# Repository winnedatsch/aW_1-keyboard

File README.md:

# aW_1 Keyboard

This repository contains the PCB, case design, and firmware for the aW_1 split (semi-)wireless keyboard. The aW_1 layout is a modification of the ErgoDox layout with straightened rows and removed thumb clusters. It is therefore fully compatible with ErgoDox keysets. It is compatible with the [ZMK](https://zmk.dev/) keyboard firmware.

## Design Philosophy
The aW_1 is based on the Nordic NRF52832 that provides both the CPU and bluetooth module in a single chip, which allows for lower power consumption. It can be operated from a standard JST-connected battery, or plugged in via USB-C, which will simultaneously charge the battery. The two keyboard halves are connected with a USB-C cable, hence the "semi"-wireless, with the right half containing most of the circuitry and the left only containing an IO expander. A different approach would be the one pursued by the Mitosis (https://www.reddit.com/r/MechanicalKeyboards/comments/66588f/wireless_split_qmk_mitosis/), which does require a dongle that both halves communicate to. I prioritized the ability to quickly connect the keyboard to laptops, mobile devices, etc. and potential pairing of multiple devices at the same time over cutting the last remaining wire. The connection between the halves is USB-C instead of TRRS because TRRS is not hot-pluggable. Like with an ErgoDox, the there is only a single reversible PCB design for both halves, which makes it cheaper to order. 

## Folder Structure
- `case`: Contains the DXF Files for a low-cost case design built from 5 layers of laser-cut acrylic. 
- `firmware/custom`: Contains a custom firmware implemented with the [Zephyr RTOS](https://www.zephyrproject.org/). The firmware implements all the essential functionality expected of a keyboard firmware (Bluetooth connectivity, layout customization, sleep mode), but lacks some important features (advanced layer config, multiple Bluetooth profiles, etc.). It has mainly served as an educational effort, but for day-to-day usage the ZMK firmware is recommended (see below).
- `firmware/zmk`: Contains the board configuration for the [ZMK](https://zmk.dev/) keyboard firmware. This firmware is recommended for regular use, as it is more stable, customizable, and offers additional features.
- `pcb`: Contains the KiCAD schematics and layout files for the reversible PCB.

## ZMK Setup & Flashing
Due to the [very strict licensing requirements of ZMK](https://zmk.dev/docs/development/clean-room), the board configuration for the GPL-licensed aW_1 cannot be added to ZMK's main repository. Fortunately, flashing the firmware is still a relatively simple process:

1. Setup ZMK locally by following its [Toolchain Setup](https://zmk.dev/docs/development/setup) guide. Let `{zmk}` be the local folder that you have cloned the ZMK main repository into. 
2. Copy the `firmware/zmk/aW_1` folder from this repository into `{zmk}/app/boards`.
3. Switch to the `{zmk}/app` folder and run `west build -b aW_1`.
4. Install the [Nordic nRF Command Line Tools](https://www.nordicsemi.com/Products/Development-tools/nrf-command-line-tools) (including the separate install of the [Segger drivers for J-Link](https://www.segger.com/downloads/jlink/#J-LinkSoftwareAndDocumentationPack) on MacOS and Linux). 
5. Connect the keyboard to your computer with your choice of [Segger J-Link](https://www.segger.com/products/debug-probes/j-link/).
6. Run `west flash` in the `{zmk}/app` directory.

That's it! Your keyboard should now show up as a Bluetooth device. If not, try restarting the keyboard by switching the power switch off and on again.

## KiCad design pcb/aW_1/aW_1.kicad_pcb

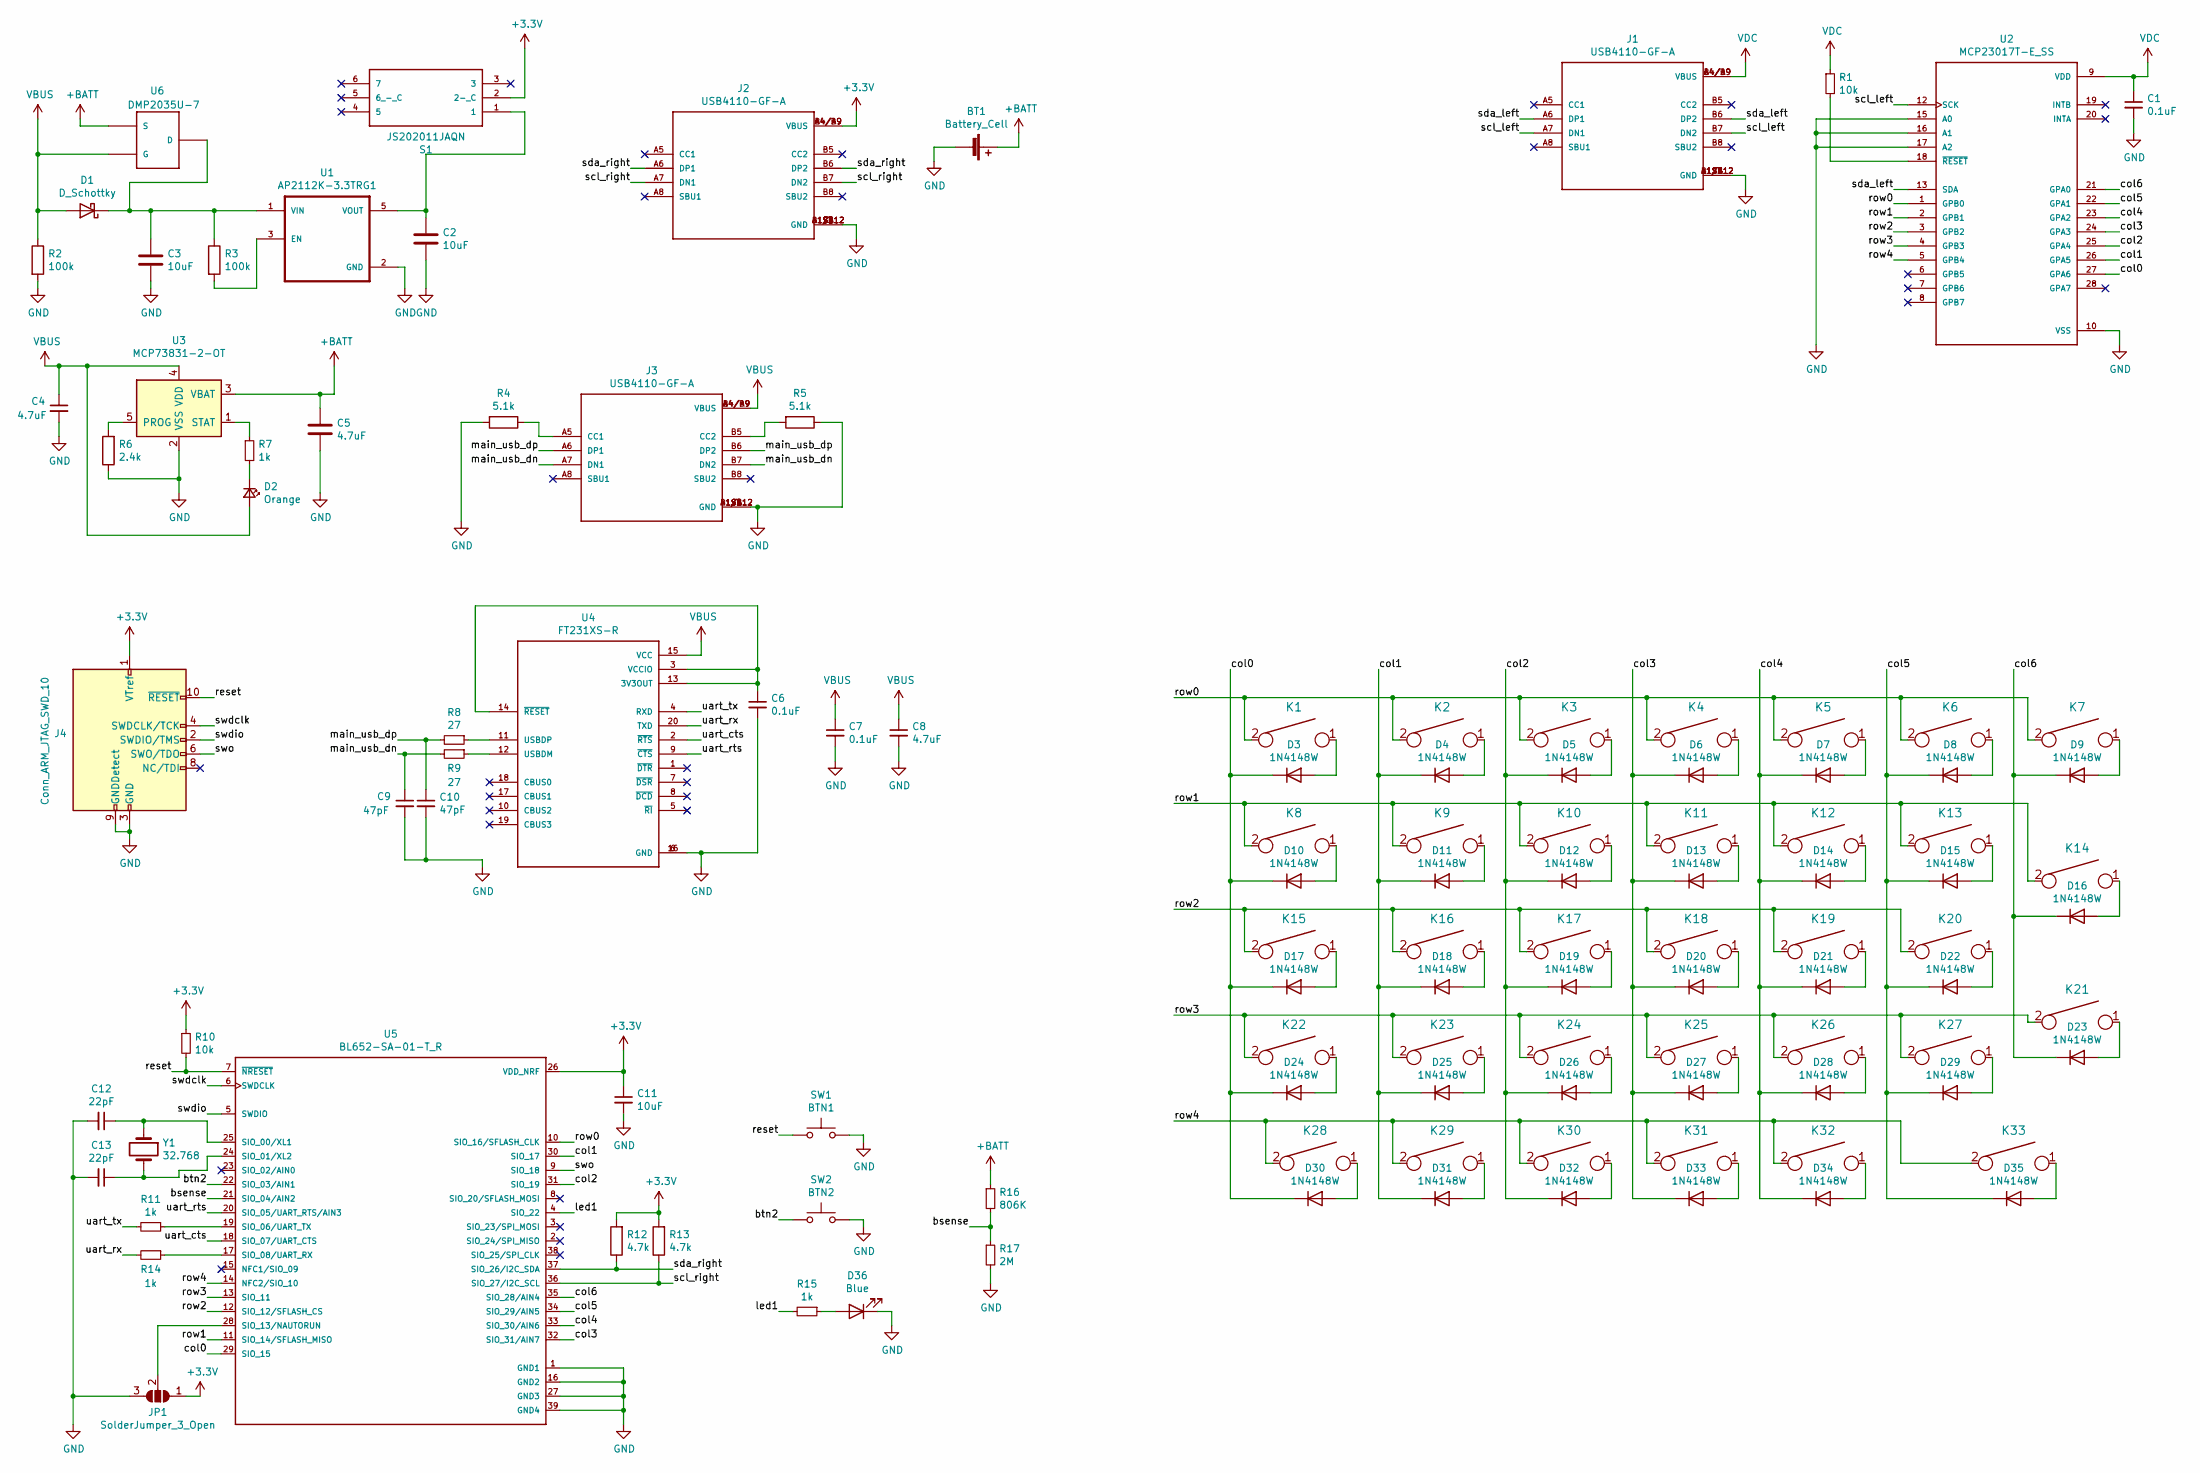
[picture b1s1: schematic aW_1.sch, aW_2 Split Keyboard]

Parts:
BT1: Battery_Cell; JST_S2B-PH-SM4-TB(LF)(SN)
C1, C6, C7: 0.1uF; C_0402_1005Metric
C2, C3, C11: 10uF; C_0603_1608Metric
C4, C5, C8: 4.7uF; C_0402_1005Metric
C9, C10: 47pF; C_0402_1005Metric
C12, C13: 22pF; C_0402_1005Metric
D1: D_Schottky; D_SOD-123
D2: Orange; LED_0805_2012Metric
D3, D4, D5, D6, D7, D8, D9, D10, D11, D12, D13, D14, D15, D16, D17, D18, D19, D20, D21, D22, D23, D24, D25, D26, D27, D28, D29, D30, D31, D32, D33, D34, D35: 1N4148W; D_SOD-123_mirrored
D36: Blue; LED_0805_2012Metric
J1, J2, J3: USB4110-GF-A; GCT_USB4110-GF-A
J4: Conn_ARM_JTAG_SWD_10; PinHeader_2x05_P1.27mm_Vertical
JP1: SolderJumper_3_Open; SolderJumper-3_P1.3mm_Open_RoundedPad1.0x1.5mm
K1, K8, K14, K15, K21, K22: KEYSW; Mx_Alps_150
K2, K3, K4, K5, K6, K7, K9, K10, K11, K12, K13, K16, K17, K18, K19, K20, K23, K24, K25, K26, K27, K28, K29, K30, K31, K32: KEYSW; Mx_Alps_100
K33: KEYSW; Mx_Alps_200
R1, R10: 10k; R_0402_1005Metric
R2, R3: 100k; R_0402_1005Metric
R4, R5: 5.1k; R_0402_1005Metric
R6: 2.4k; R_0402_1005Metric
R7, R11, R14, R15: 1k; R_0402_1005Metric
R8, R9: 27; R_0402_1005Metric
R12, R13: 4.7k; R_0402_1005Metric
R16: 806K; R_0603_1608Metric
R17: 2M; R_0603_1608Metric
S1: JS202011JAQN
SW1: BTN1; SW_KMR221GLFS
SW2: BTN2; SW_KMR221GLFS
U1: AP2112K-3.3TRG1; SOT95P285X140-5N
U2: MCP23017T-E_SS; SOP65P780X200-28N
U3: MCP73831-2-OT; SOT-23-5
U4: FT231XS-R; SOP63P599X175-20N
U5: BL652-SA-01-T_R; XCVR_BL652-SA-01-T
U6: DMP2035U-7; SOT23
Y1: 32.768; XTAL_ECS-.327-12.5-34B-TR

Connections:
+3V3: C11.1, J2.A4/B9 (VBUS), J2.B4/A9 (VBUS), J4.1 (VTref), JP1.1 (A), R10.1, R12.2, R13.2, S1.2 (2-_C), U5.26 (VDD_NRF)
+BATT: BT1.1 (+), C5.1, R16.1, U3.3 (VBAT), U6.2 (S)
/bsense: R16.2, R17.1, U5.21 (SIO_04/AIN2)
/btn2: SW2.1, U5.22 (SIO_03/AIN1)
/col0: D3.1 (K), D10.1 (K), D17.1 (K), D24.1 (K), D30.1 (K), U2.27 (GPA6), U5.29 (SIO_15)
/col1: D4.1 (K), D11.1 (K), D18.1 (K), D25.1 (K), D31.1 (K), U2.26 (GPA5), U5.30 (SIO_17)
/col2: D5.1 (K), D12.1 (K), D19.1 (K), D26.1 (K), D32.1 (K), U2.25 (GPA4), U5.31 (SIO_19)
/col3: D6.1 (K), D13.1 (K), D20.1 (K), D27.1 (K), D33.1 (K), U2.24 (GPA3), U5.32 (SIO_31/AIN7)
/col4: D7.1 (K), D14.1 (K), D21.1 (K), D28.1 (K), D34.1 (K), U2.23 (GPA2), U5.33 (SIO_30/AIN6)
/col5: D8.1 (K), D15.1 (K), D22.1 (K), D29.1 (K), D35.1 (K), U2.22 (GPA1), U5.34 (SIO_29/AIN5)
/col6: D9.1 (K), D16.1 (K), D23.1 (K), U2.21 (GPA0), U5.35 (SIO_28/AIN4)
/led1: R15.2, U5.4 (SIO_22)
/main_usb_dn: C9.1, J3.A7 (DN1), J3.B7 (DN2), R9.2
/main_usb_dp: C10.1, J3.A6 (DP1), J3.B6 (DP2), R8.2
/reset: J4.10 (~RESET~), R10.2, SW1.1, U5.7 (~NRESET~)
/row0: K1.2, K2.2, K3.2, K4.2, K5.2, K6.2, K7.2, U2.1 (GPB0), U5.10 (SIO_16/SFLASH_CLK)
/row1: K8.2, K9.2, K10.2, K11.2, K12.2, K13.2, K14.2, U2.2 (GPB1), U5.11 (SIO_14/SFLASH_MISO)
/row2: K15.2, K16.2, K17.2, K18.2, K19.2, K20.2, U2.3 (GPB2), U5.12 (SIO_12/SFLASH_CS)
/row3: K21.2, K22.2, K23.2, K24.2, K25.2, K26.2, K27.2, U2.4 (GPB3), U5.13 (SIO_11)
/row4: K28.2, K29.2, K30.2, K31.2, K32.2, K33.2, U2.5 (GPB4), U5.14 (NFC2/SIO_10)
/scl_left: J1.A7 (DN1), J1.B7 (DN2), U2.12 (SCK)
/scl_right: J2.A7 (DN1), J2.B7 (DN2), R13.1, U5.36 (SIO_27/I2C_SCL)
/sda_left: J1.A6 (DP1), J1.B6 (DP2), U2.13 (SDA)
/sda_right: J2.A6 (DP1), J2.B6 (DP2), R12.1, U5.37 (SIO_26/I2C_SDA)
/swdclk: J4.4 (SWDCLK/TCK), U5.6 (SWDCLK)
/swdio: J4.2 (SWDIO/TMS), U5.5 (SWDIO)
/swo: J4.6 (SWO/TDO), U5.9 (SIO_18)
/uart_cts: U4.2 (~RTS~), U5.18 (SIO_07/UART_CTS)
/uart_rts: U4.9 (~CTS~), U5.20 (SIO_05/UART_RTS/AIN3)
/uart_rx: R14.2, U4.20 (TXD)
/uart_tx: R11.2, U4.4 (RXD)
GND: BT1.2 (-), C1.2, C2.2, C3.2, C4.2, C5.2, C6.2, C7.2, C8.2, C9.2, C10.2, C11.2, C12.2, C13.2, D36.1 (K), J1.A1/B12 (GND), J1.B1/A12 (GND), J1.S1 (GND), J1.S2 (GND), J1.S3 (GND), J1.S4 (GND), J2.A1/B12 (GND), J2.B1/A12 (GND), J2.S1 (GND), J2.S2 (GND), J2.S3 (GND), J2.S4 (GND), J3.A1/B12 (GND), J3.B1/A12 (GND), J3.S1 (GND), J3.S2 (GND), J3.S3 (GND), J3.S4 (GND), J4.3 (GND), J4.5 (GND), J4.9 (GNDDetect), JP1.3 (B), R2.2, R4.2, R5.1, R6.1, R17.2, SW1.2, SW2.2, U1.2 (GND), U2.10 (VSS), U2.15 (A0), U2.16 (A1), U2.17 (A2), U3.2 (VSS), U4.6 (GND), U4.16 (GND), U5.1 (GND1), U5.16 (GND2), U5.27 (GND3), U5.39 (GND4)
unnamed: C2.1, S1.1, U1.5 (VOUT)
unnamed: C3.1, D1.1 (K), R3.1, U1.1 (VIN), U6.3 (D)
unnamed: C6.1, U4.3 (VCCIO), U4.13 (3V3OUT), U4.14 (~RESET~)
unnamed: C12.1, U5.25 (SIO_00/XL1), Y1.1
unnamed: C13.1, U5.24 (SIO_01/XL2), Y1.2
unnamed: D2.1 (K), R7.2
unnamed: D3.2 (A), K1.1
unnamed: D4.2 (A), K2.1
unnamed: D5.2 (A), K3.1
unnamed: D6.2 (A), K4.1
unnamed: D7.2 (A), K5.1
unnamed: D8.2 (A), K6.1
unnamed: D9.2 (A), K7.1
unnamed: D10.2 (A), K8.1
unnamed: D11.2 (A), K9.1
unnamed: D12.2 (A), K10.1
unnamed: D13.2 (A), K11.1
unnamed: D14.2 (A), K12.1
unnamed: D15.2 (A), K13.1
unnamed: D16.2 (A), K14.1
unnamed: D17.2 (A), K15.1
unnamed: D18.2 (A), K16.1
unnamed: D19.2 (A), K17.1
unnamed: D20.2 (A), K18.1
unnamed: D21.2 (A), K19.1
unnamed: D22.2 (A), K20.1
unnamed: D23.2 (A), K21.1
unnamed: D24.2 (A), K22.1
unnamed: D25.2 (A), K23.1
unnamed: D26.2 (A), K24.1
unnamed: D27.2 (A), K25.1
unnamed: D28.2 (A), K26.1
unnamed: D29.2 (A), K27.1
unnamed: D30.2 (A), K28.1
unnamed: D31.2 (A), K29.1
unnamed: D32.2 (A), K30.1
unnamed: D33.2 (A), K31.1
unnamed: D34.2 (A), K32.1
unnamed: D35.2 (A), K33.1
unnamed: D36.2 (A), R15.1
unnamed: J3.A5 (CC1), R4.1
unnamed: J3.B5 (CC2), R5.2
unnamed: JP1.2 (C), U5.28 (SIO_13/NAUTORUN)
unnamed: R1.2, U2.18 (~RESET~)
unnamed: R3.2, U1.3 (EN)
unnamed: R6.2, U3.5 (PROG)
unnamed: R7.1, U3.1 (STAT)
unnamed: R8.1, U4.11 (USBDP)
unnamed: R9.1, U4.12 (USBDM)
unnamed: R11.1, U5.19 (SIO_06/UART_TX)
unnamed: R14.1, U5.17 (SIO_08/UART_RX)
VBUS: C4.1, C7.1, C8.1, D1.2 (A), D2.2 (A), J3.A4/B9 (VBUS), J3.B4/A9 (VBUS), R2.1, U3.4 (VDD), U4.15 (VCC), U6.1 (G)
VDC: C1.1, J1.A4/B9 (VBUS), J1.B4/A9 (VBUS), R1.1, U2.9 (VDD)

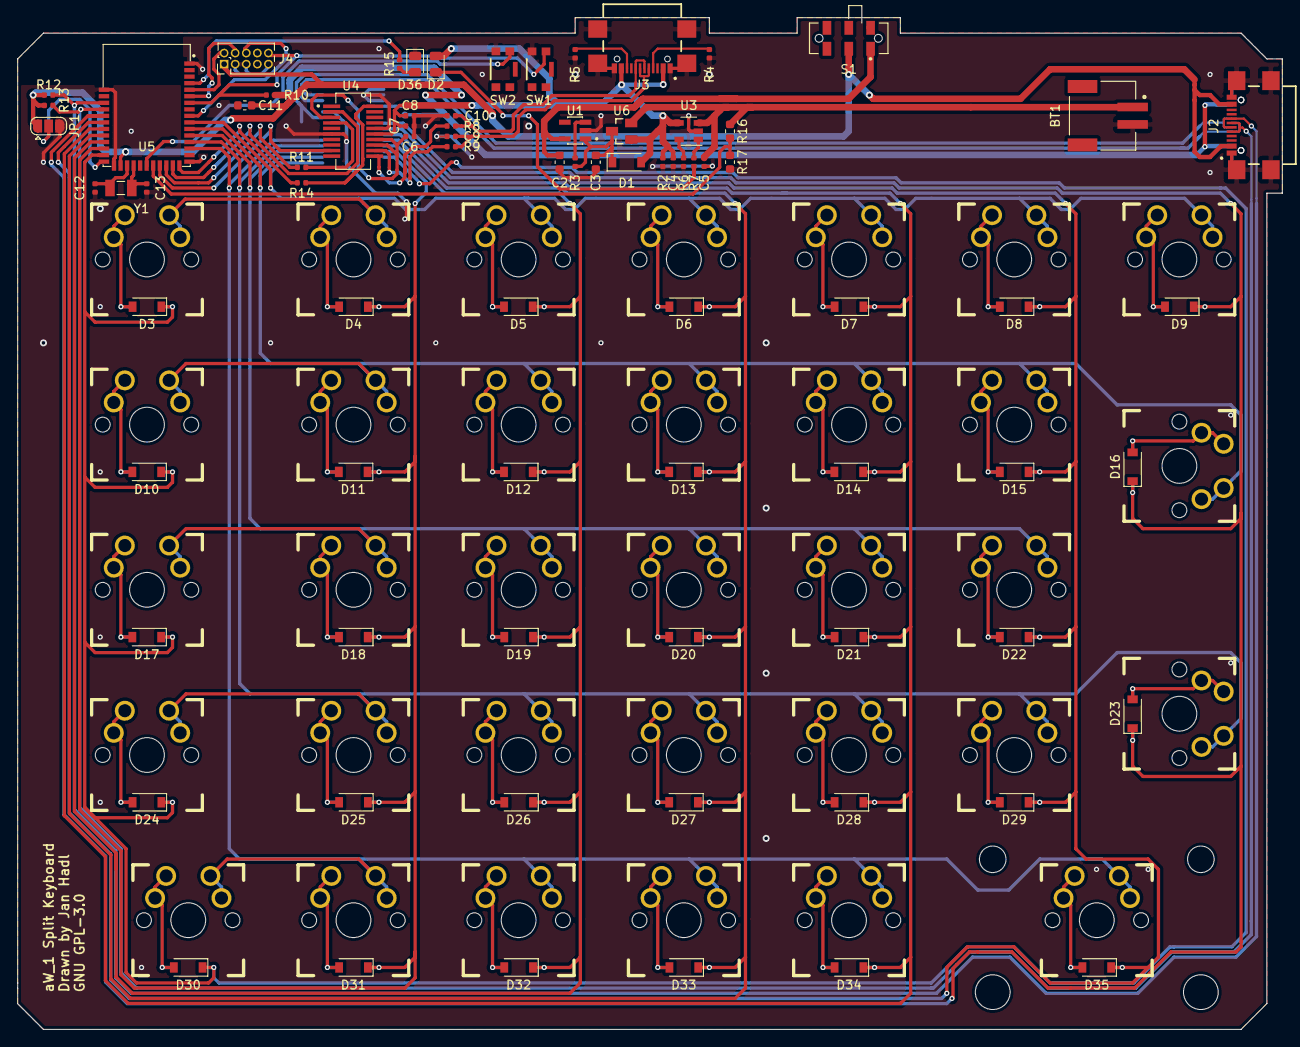
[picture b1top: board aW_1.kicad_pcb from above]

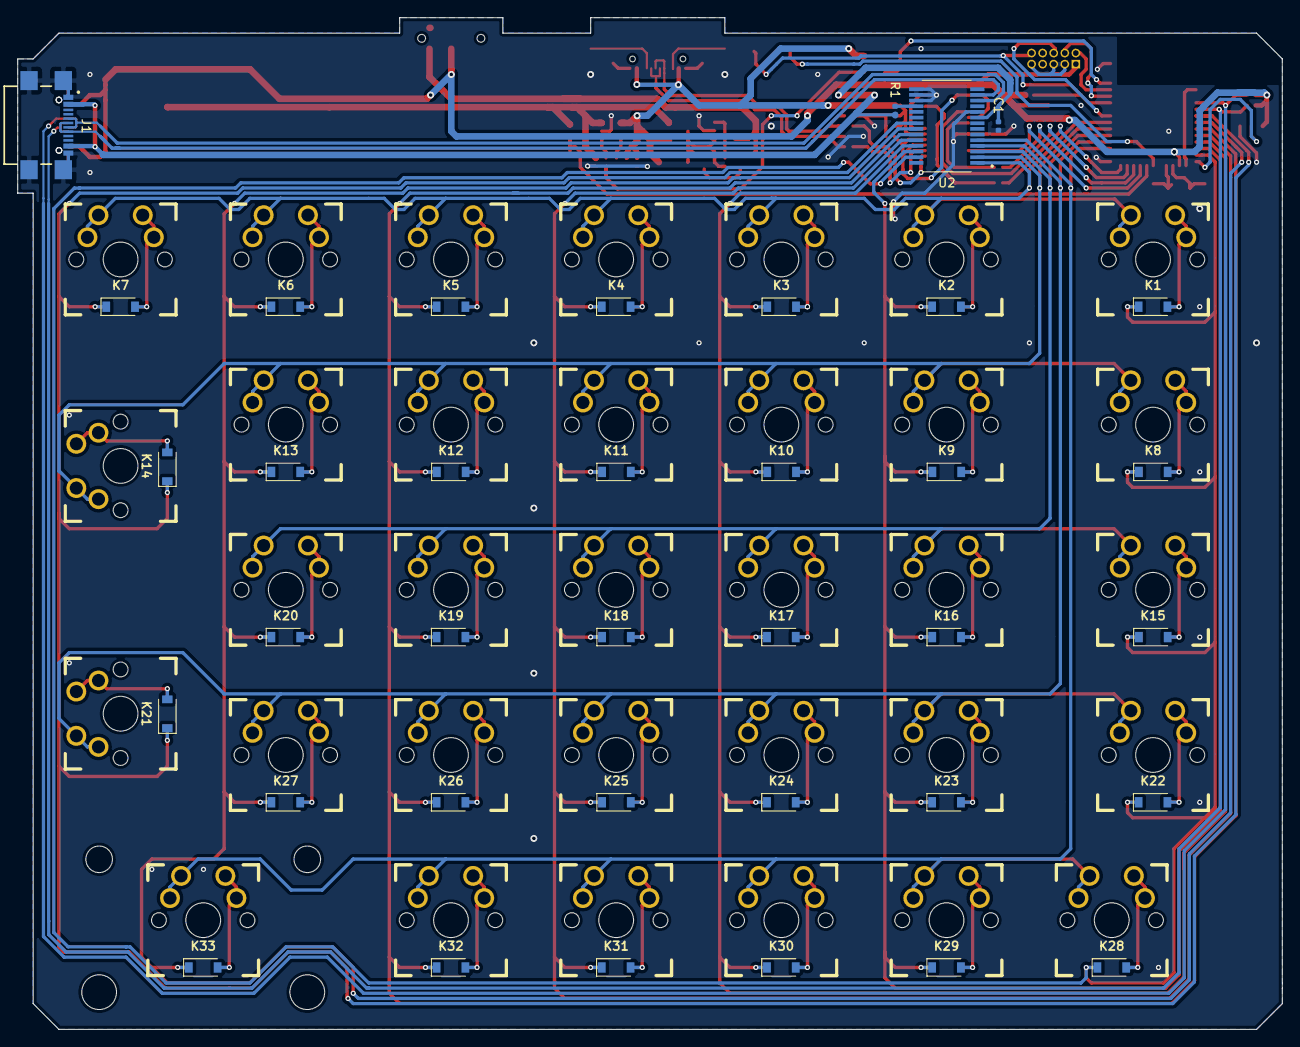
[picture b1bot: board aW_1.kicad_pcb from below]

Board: 2 copper layers, 145.1 x 116.1 mm, 115 parts (4 on the bottom side), 85 nets.

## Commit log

2020-04-10 Zephyr and PlatformIO board config; blinky example
2020-04-11 Converted code to CPP, added matrix scanning code
2020-04-19 Incomplete implementation of BLE HID service
2020-04-22 modified BLE hid implementation, but not working yet
2020-04-26 Fixed HID config, input works now; connection on mobile still fails
2020-05-11 added battery reporting
2020-05-15 Added support for left keyboard half over i2c
2020-05-24 first draft of board schematic
2020-05-31 Added USB controller and reset button
2020-06-01 Added additional leds and buttons, decoupling capacitors, component mappings
2020-06-14 Finished keyboard matrix wiring, left side wiring
2020-06-19 (Almost) finished pcb, few GND connections missing
2020-06-21 Traces and pours finished
2020-06-24 Fixed silk screen and fab layers
2020-06-26 Added gerbers, license information, updated connector information
2020-06-26 Renamed all references to aW_2 to aW_1, added readme
2020-06-26 Added PCB preview to readme
2020-06-26 Added license
2020-06-26 updated readme to reflect project status
2020-07-01 Added voltage divider for battery measurement, improved gnd pour
2020-07-02 Cleaned up layout, updated gerbers
2020-07-02 Modified traces around spacebar stab mounts for additional clearance
2020-07-04 Fixed mosfet and improved keepout around antenna
2020-07-04 Added 1mm of clearance to the bottom side (for spacebar mounting holes)
2020-07-18 extracted matrix scanning and connection management into separate files
2020-07-19 added keycode resolver, fixed battery reader
2020-08-09 Added include guards, updated board definition
2020-08-09 Enabled DCDC mode, fixed mirrored key resolving for right half, made battery pin configurable, fixed NFC pin not being GPIO
2020-08-09 Updated PCB preview
2020-08-09 Fixed README typo
2020-08-09 Add back left-half scanning
2020-08-14 added proper environment config, fn layer, replaced raw pointers with smart ptrs, added case dxf files
2020-08-14 fixed board mappings typo
2020-08-16 Improved battery efficiency, BLE handling
2020-08-17 Added DIS parameter, boot report & protocol mode characteristics
2020-08-17 added output report characteristic for led hid output
2020-08-18 added callbacks to all HID GATT attributes, formatted all source files
2020-08-25 Added case fixes from first prototype, and modifications for Adafruit battery compatibility
2020-08-26 updated to latest zephyr version
2020-09-17 fixed keymap
2020-09-18 Improved advertising handling and added button for clearing pairing info
2020-09-18 Replaced printk with proper logging calls
2020-09-25 Increased TX Power to +4dBm (maximum), decreased advertising interval for faster reconnection
2020-10-07 added bom
2020-10-30 Tightened connection intervals and sleep times for faster keyboard feel
2024-03-01 added zmk board configuration; additional images; updated readme

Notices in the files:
pcb/aW_1/aW_1.kicad_pcb:
License: GNU GPL-3.0
GNU GPL-3.0
